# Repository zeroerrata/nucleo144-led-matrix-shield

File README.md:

<p align="center">
  <a href="https://zeroerrata.eu"><picture>
    <source media="(prefers-color-scheme: dark)" srcset="images/zeroerrata-logo-dark.png">
    
  </picture></a>
</p>

<h1 align="center">Nucleo-144 LED matrix shield: 1860 LEDs</h1>

<p align="center"><b>A full-size Nucleo-144 shield with a 31 x 60 matrix of red 0402 LEDs at 45 degrees, driven by constant-current sinks.</b></p>

<p align="center">
  
</p>

<p align="center">

</p>

## About

A display shield for STM32 Nucleo-144 boards (ST morpho connectors CN11 / CN12): 31 columns by 60 rows = 1860 red 0402 LEDs on a 1.75 mm square pitch, every LED turned 45 degrees, filling the whole Nucleo-144 outline. Columns are switched to +5 V by P-MOSFETs selected through four 3-to-8 decoders, rows are sunk by four 16-channel constant-current LED drivers at 5.7 mA per LED, and one column is lit at a time (1/31 duty), refreshed by the Nucleo's MCU.

A dense 4-layer board: rows on the top layer, a solid ground plane, column lanes and the switched column supplies on the inner and bottom layers.

## Features

- 1860 red 0402 LEDs (31 x 60) on a 1.75 mm pitch, rotated 45 degrees for a diamond pattern
- 4 x STP16CP05 constant-current row sinks (5.7 mA per LED, one resistor sets the current)
- 31 x AO3401A P-MOSFET column switches, selected by 4 x 74AHCT138 decoders
- Up to 341 mA in one column from the Nucleo +5 V; driver logic on +3.3 V
- Fits the Nucleo-144 outline and plugs into the ST morpho headers (NUCLEO-F429ZI / F767ZI family)
- One-sided JLCPCB assembly; the morpho sockets are hand-soldered

## Specifications

| | |
|---|---|
| Board | 70.0 x 133.4 mm, 4 copper layers, 1.6 mm |
| Finish | ENIG |
| Parts | 1927 |
| Release | rev 4, 2026-11-27 |
| LED matrix | 31 x 60 = 1860, red, 0402, 1.75 mm pitch |
| Host | STM32 Nucleo-144 (ST morpho CN11 / CN12) |
| Supply | +5 V and +3.3 V from the Nucleo |
| Stackup | 4 layers, 1.6 mm |

## Design values

- 5.7 mA per LED set by the drivers' current resistors; one column of up to 60 LEDs lit at a time: up to 341 mA from the Nucleo +5 V.
- 1/31 duty multiplex, refreshed by the Nucleo MCU.

## Renders

Full resolution: [isometric view](images/renders/hero_iso.png), [top side](images/renders/top.png), [bottom side](images/renders/bottom.png), [low-angle view](images/renders/low.png).

## Files

| Folder | Contents |
|---|---|
| [`kicad/`](kicad) | KiCad 10 project: schematic, board, design rules, project libraries |
| [`docs/`](docs) | [schematic.pdf](docs/schematic.pdf), [board_layers.pdf](docs/board_layers.pdf) |
| [`fabrication/`](fabrication) | Gerber and drill files (zip), bill of materials, pick-and-place |
| [`images/`](images) | renders and copper layer pictures |
| [`analysis/`](analysis) | simulation and analysis results: bringup, dfm, retpath |

## Verification

- MCU pin map checked against the NUCLEO-F429ZI connector tables
- Every result is a prediction from design data; the board has not been measured unless stated.

## How to order

1. Upload `fabrication/gerbers_drill.zip` to your PCB fab; the stackup and finish are in the specifications above.
2. For assembly, use `fabrication/bom_jlcpcb.csv` and `fabrication/cpl_jlcpcb.csv` (JLCPCB format) or the KiCad-format `bom.csv` / `pos.csv`.
3. Check part stock and the footprints against the current data sheets before you order.

## Known issues

Found by the design review of this release; boards built from these files carry them:

- Crosstalk: the bottom drivers' clock couples a 0.73 V spike into their output-enable line (simulated). It stays below the logic threshold, so at worst a nanosecond dimming glitch; firmware avoids it by shifting column data while the outputs are off. Rev 4 re-routes these lines; the crosstalk check passes.
- Reflow balance: from rev 4 the small ground pads connect through thermal reliefs; use a profile with a 60-90 s soak at 150-180 C and inspect the 0402 resistors.
- Parts: rev 4 orders Samtec SSQ-135-01-T-D morpho sockets (second source Sullins PPPC352LFBN-RC) and current 22 uF capacitors; the STP16CP05TTR row drivers had little stock in 2026: buy the drivers before ordering boards.

## Notes

- The renders show the ZeroErrata house look; from rev 4 the fabrication package specifies it too: matte black solder mask, white silkscreen, ENIG.
- The firmware (column scan) is not part of this repository.

## Licence

Released under the [CERN Open Hardware Licence Version 2 - Permissive](LICENSE) (CERN-OHL-P-2.0): use, modify, make and sell it, also commercially. Provided as is, without warranty.

---

<p align="center">
  Designed by <a href="https://zeroerrata.eu"><b>ZeroErrata</b></a>: PCB design, verified before it is ordered.<br>
  <a href="https://zeroerrata.eu">zeroerrata.eu</a> · <a href="mailto:hello@zeroerrata.eu">hello@zeroerrata.eu</a>
</p>

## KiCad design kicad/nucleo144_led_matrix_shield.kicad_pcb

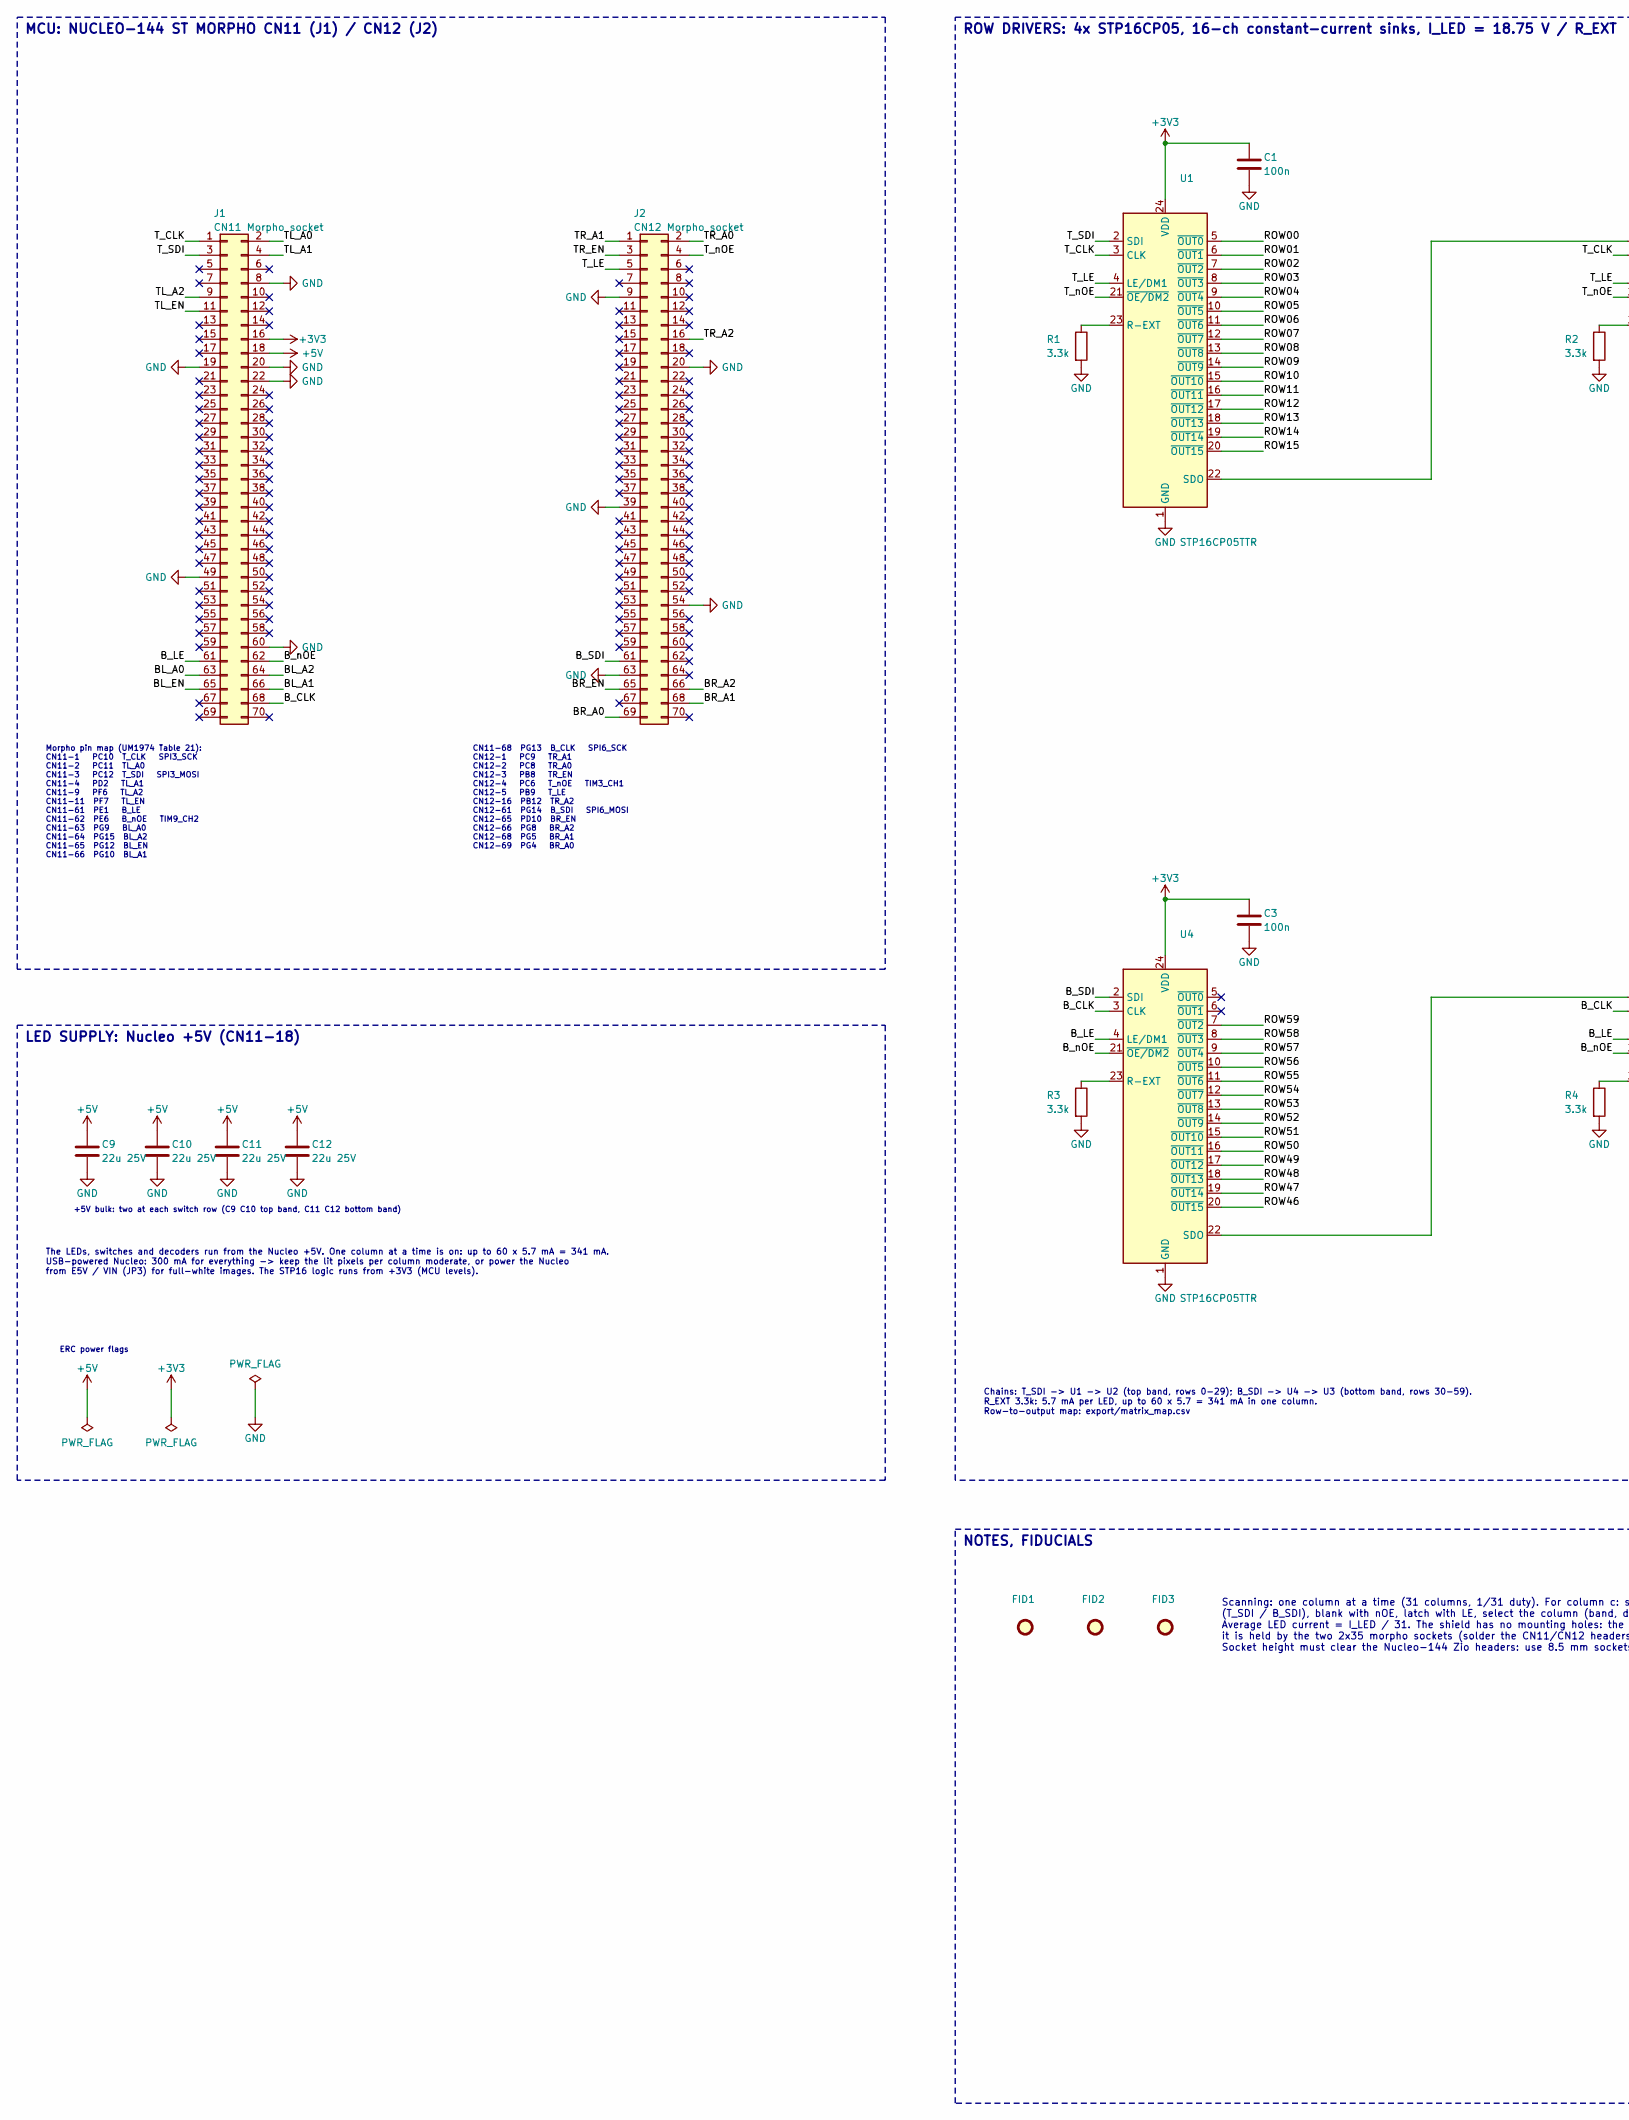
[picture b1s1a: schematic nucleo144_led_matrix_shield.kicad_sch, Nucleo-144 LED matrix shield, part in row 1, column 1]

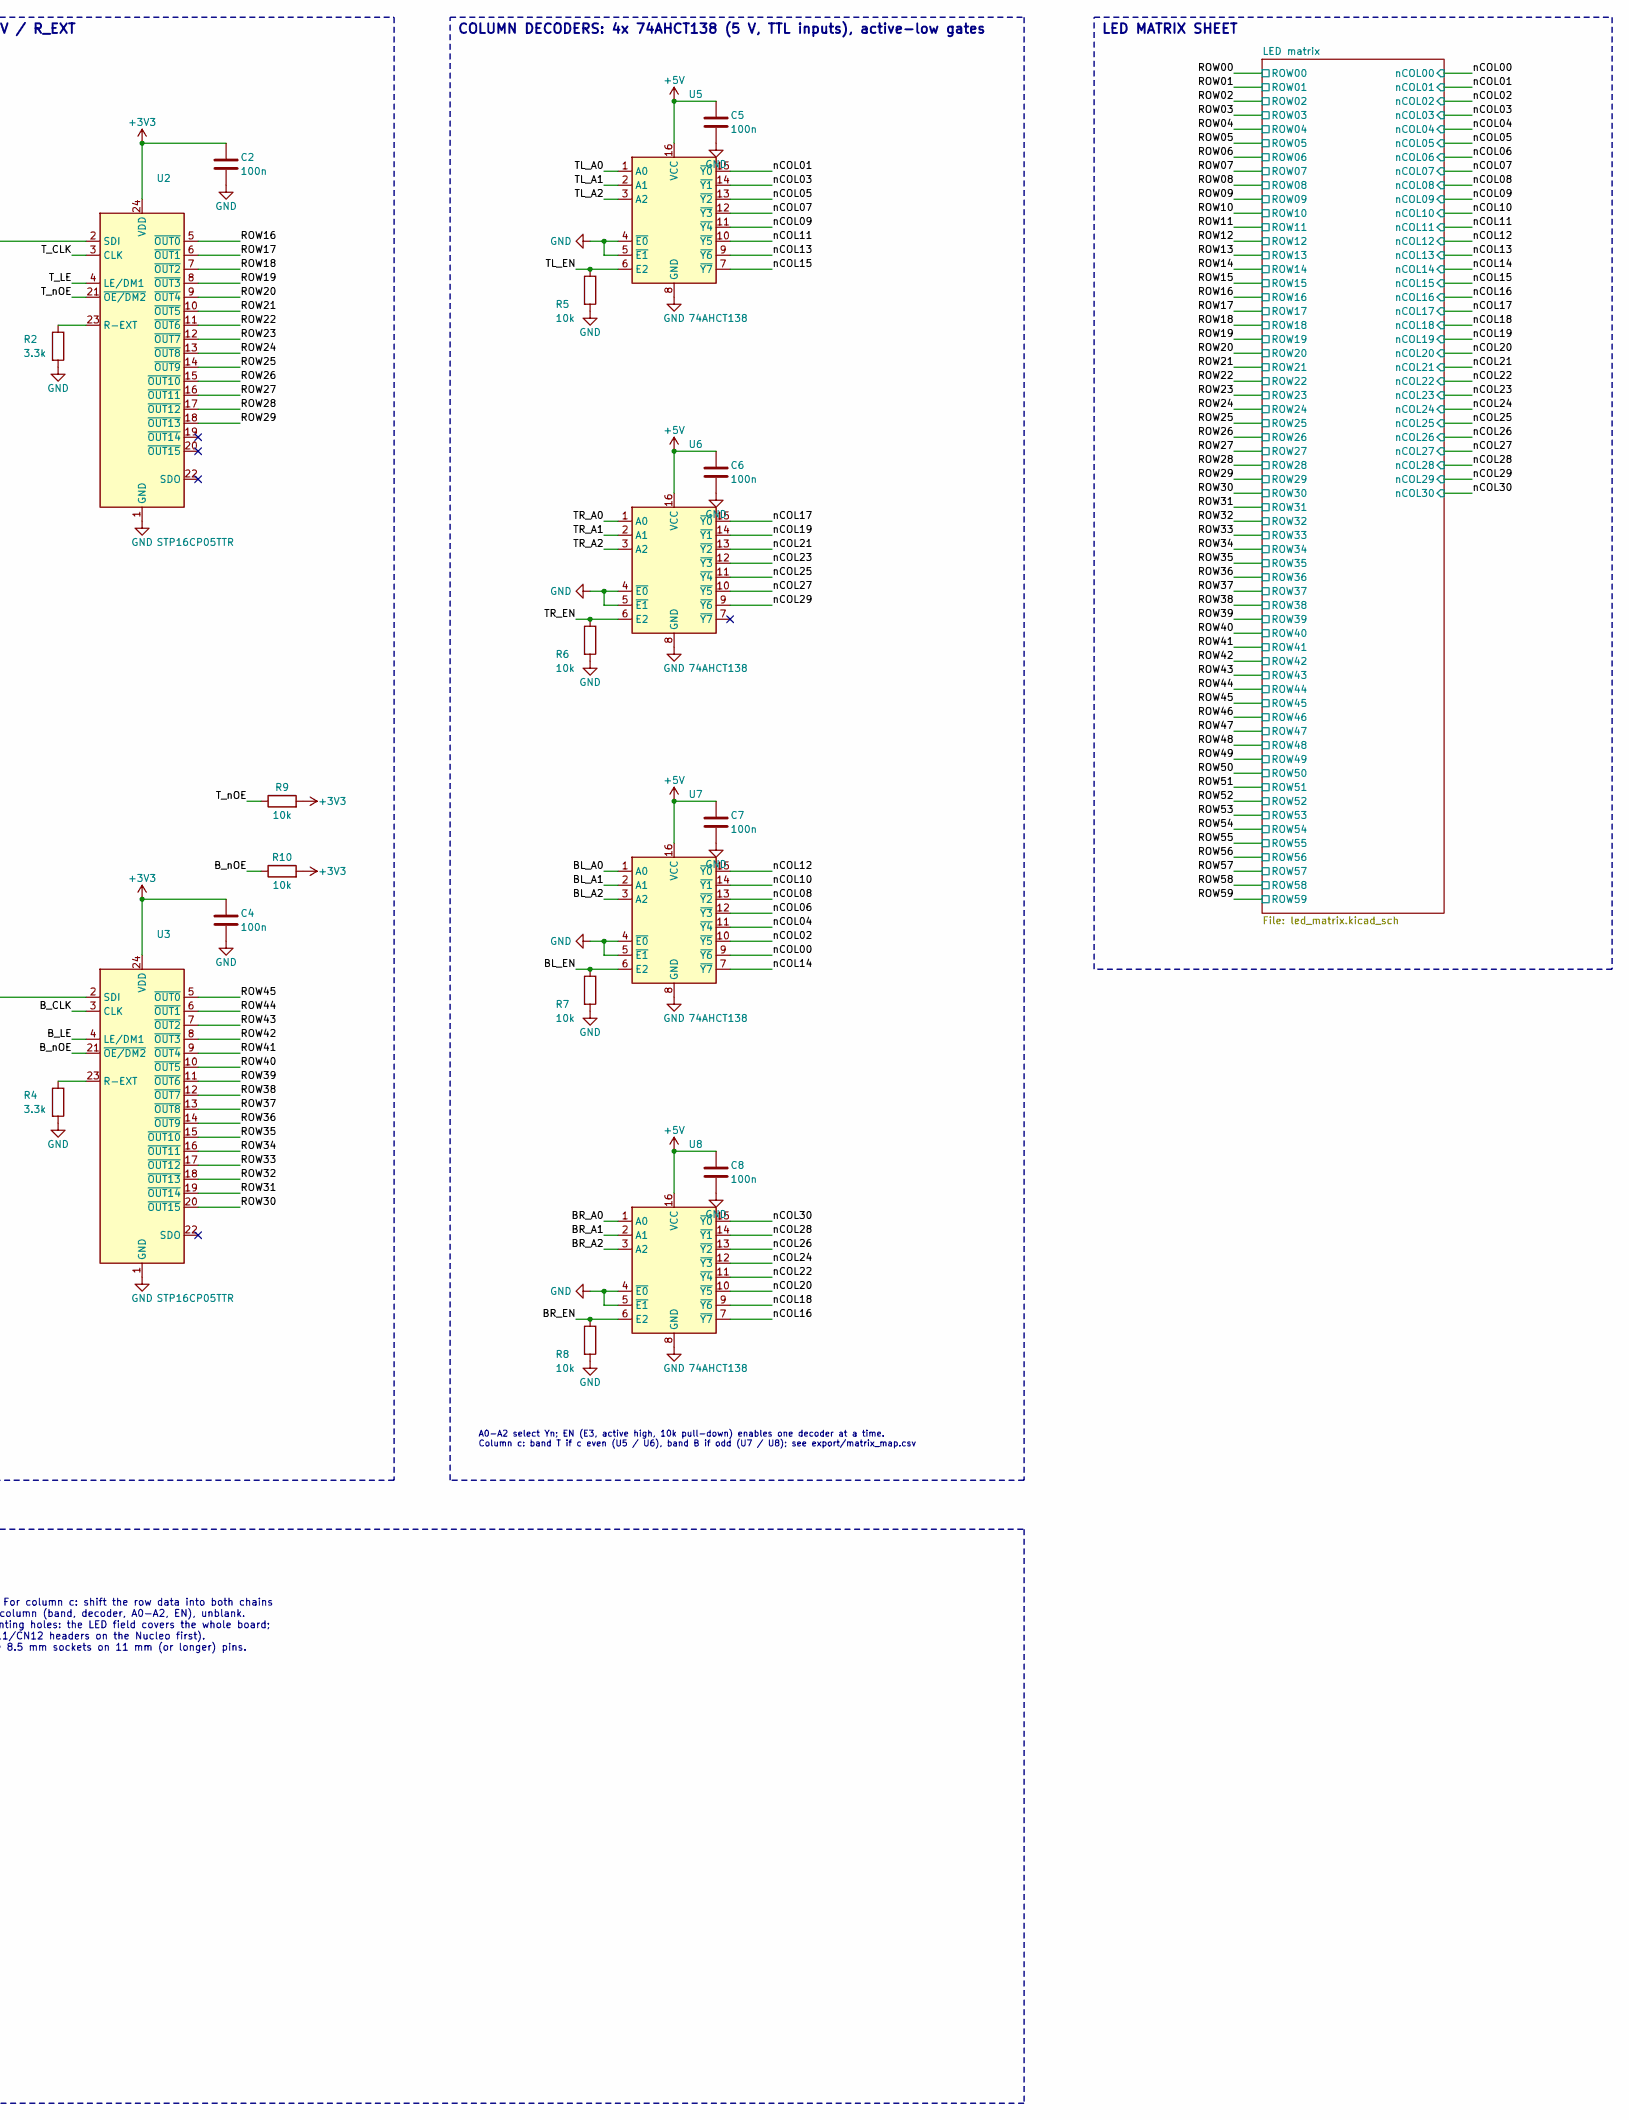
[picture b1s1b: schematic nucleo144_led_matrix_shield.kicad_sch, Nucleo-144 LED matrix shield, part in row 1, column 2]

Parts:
C1, C2, C3, C4, C5, C6, C7, C8: 100n; C_0402_1005Metric; MPN CL05B104KO5NNNC; LCSC C1525
C9, C10, C11, C12: 22u 25V; C_0805_2012Metric; MPN CL21A226MAYNNNE; LCSC C602037
FID1, FID2, FID3: Fiducial; Fiducial_1mm_Mask2mm
J1: CN11 Morpho socket; Morpho_2x35_P2.54mm_Socket_NoInnerAnnulus; MPN SSQ-135-01-T-D; LCSC C7088697
J2: CN12 Morpho socket; Morpho_2x35_P2.54mm_Socket_NoInnerAnnulus; MPN SSQ-135-01-T-D; LCSC C7088697
R1, R2, R3, R4: 3.3k; R_0402_1005Metric; MPN 0402WGF3301TCE; LCSC C25890
R5, R6, R7, R8, R9, R10: 10k; R_0402_1005Metric; MPN 0402WGF1002TCE; LCSC C25744
U1, U2, U3, U4: STP16CP05TTR; TSSOP-24_4.4x7.8mm_P0.65mm; MPN STP16CP05TTR; LCSC C127267
U5, U6, U7, U8: 74AHCT138; TSSOP-16_4.4x5mm_P0.65mm; MPN SN74AHCT138PWR; LCSC C8205

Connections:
+3V3: C1.1, C2.1, C3.1, C4.1, J1.16, R9.2, R10.2, U1.24 (VDD), U2.24 (VDD), U3.24 (VDD), U4.24 (VDD)
+5V: C5.1, C6.1, C7.1, C8.1, C9.1, C10.1, C11.1, C12.1, J1.18, U5.16 (VCC), U6.16 (VCC), U7.16 (VCC), U8.16 (VCC); also elsewhere on the board
/BL_A0: J1.63, U7.1 (A0)
/BL_A1: J1.66, U7.2 (A1)
/BL_A2: J1.64, U7.3 (A2)
/BL_EN: J1.65, R7.1, U7.6 (E2)
/BR_A0: J2.69, U8.1 (A0)
/BR_A1: J2.68, U8.2 (A1)
/BR_A2: J2.66, U8.3 (A2)
/BR_EN: J2.65, R8.1, U8.6 (E2)
/B_CLK: J1.68, U3.3 (CLK), U4.3 (CLK)
/B_LE: J1.61, U3.4 (LE/DM1), U4.4 (LE/DM1)
/B_SDI: J2.61, U4.2 (SDI)
/B_nOE: J1.62, R10.1, U3.21 (~OE/DM2), U4.21 (~OE/DM2)
/ROW00: U1.5 (~OUT0); also elsewhere on the board
/ROW01: U1.6 (~OUT1); also elsewhere on the board
/ROW02: U1.7 (~OUT2); also elsewhere on the board
/ROW03: U1.8 (~OUT3); also elsewhere on the board
/ROW04: U1.9 (~OUT4); also elsewhere on the board
/ROW05: U1.10 (~OUT5); also elsewhere on the board
/ROW06: U1.11 (~OUT6); also elsewhere on the board
/ROW07: U1.12 (~OUT7); also elsewhere on the board
/ROW08: U1.13 (~OUT8); also elsewhere on the board
/ROW09: U1.14 (~OUT9); also elsewhere on the board
/ROW10: U1.15 (~OUT10); also elsewhere on the board
/ROW11: U1.16 (~OUT11); also elsewhere on the board
/ROW12: U1.17 (~OUT12); also elsewhere on the board
/ROW13: U1.18 (~OUT13); also elsewhere on the board
/ROW14: U1.19 (~OUT14); also elsewhere on the board
/ROW15: U1.20 (~OUT15); also elsewhere on the board
/ROW16: U2.5 (~OUT0); also elsewhere on the board
/ROW17: U2.6 (~OUT1); also elsewhere on the board
/ROW18: U2.7 (~OUT2); also elsewhere on the board
/ROW19: U2.8 (~OUT3); also elsewhere on the board
/ROW20: U2.9 (~OUT4); also elsewhere on the board
/ROW21: U2.10 (~OUT5); also elsewhere on the board
/ROW22: U2.11 (~OUT6); also elsewhere on the board
/ROW23: U2.12 (~OUT7); also elsewhere on the board
/ROW24: U2.13 (~OUT8); also elsewhere on the board
/ROW25: U2.14 (~OUT9); also elsewhere on the board
/ROW26: U2.15 (~OUT10); also elsewhere on the board
/ROW27: U2.16 (~OUT11); also elsewhere on the board
/ROW28: U2.17 (~OUT12); also elsewhere on the board
/ROW29: U2.18 (~OUT13); also elsewhere on the board
/ROW30: U3.20 (~OUT15); also elsewhere on the board
/ROW31: U3.19 (~OUT14); also elsewhere on the board
/ROW32: U3.18 (~OUT13); also elsewhere on the board
/ROW33: U3.17 (~OUT12); also elsewhere on the board
/ROW34: U3.16 (~OUT11); also elsewhere on the board
/ROW35: U3.15 (~OUT10); also elsewhere on the board
/ROW36: U3.14 (~OUT9); also elsewhere on the board
/ROW37: U3.13 (~OUT8); also elsewhere on the board
/ROW38: U3.12 (~OUT7); also elsewhere on the board
/ROW39: U3.11 (~OUT6); also elsewhere on the board
/ROW40: U3.10 (~OUT5); also elsewhere on the board
/ROW41: U3.9 (~OUT4); also elsewhere on the board
/ROW42: U3.8 (~OUT3); also elsewhere on the board
/ROW43: U3.7 (~OUT2); also elsewhere on the board
/ROW44: U3.6 (~OUT1); also elsewhere on the board
/ROW45: U3.5 (~OUT0); also elsewhere on the board
/ROW46: U4.20 (~OUT15); also elsewhere on the board
/ROW47: U4.19 (~OUT14); also elsewhere on the board
/ROW48: U4.18 (~OUT13); also elsewhere on the board
/ROW49: U4.17 (~OUT12); also elsewhere on the board
/ROW50: U4.16 (~OUT11); also elsewhere on the board
/ROW51: U4.15 (~OUT10); also elsewhere on the board
/ROW52: U4.14 (~OUT9); also elsewhere on the board
/ROW53: U4.13 (~OUT8); also elsewhere on the board
/ROW54: U4.12 (~OUT7); also elsewhere on the board
/ROW55: U4.11 (~OUT6); also elsewhere on the board
/ROW56: U4.10 (~OUT5); also elsewhere on the board
/ROW57: U4.9 (~OUT4); also elsewhere on the board
/ROW58: U4.8 (~OUT3); also elsewhere on the board
/ROW59: U4.7 (~OUT2); also elsewhere on the board
/TL_A0: J1.2, U5.1 (A0)
/TL_A1: J1.4, U5.2 (A1)
/TL_A2: J1.9, U5.3 (A2)
/TL_EN: J1.11, R5.1, U5.6 (E2)
/TR_A0: J2.2, U6.1 (A0)
/TR_A1: J2.1, U6.2 (A1)
/TR_A2: J2.16, U6.3 (A2)
/TR_EN: J2.3, R6.1, U6.6 (E2)
/T_CLK: J1.1, U1.3 (CLK), U2.3 (CLK)
/T_LE: J2.5, U1.4 (LE/DM1), U2.4 (LE/DM1)
/T_SDI: J1.3, U1.2 (SDI)
/T_nOE: J2.4, R9.1, U1.21 (~OE/DM2), U2.21 (~OE/DM2)
/nCOL00: U7.9 (~Y6); also elsewhere on the board
/nCOL01: U5.15 (~Y0); also elsewhere on the board
/nCOL02: U7.10 (~Y5); also elsewhere on the board
/nCOL03: U5.14 (~Y1); also elsewhere on the board
/nCOL04: U7.11 (~Y4); also elsewhere on the board
/nCOL05: U5.13 (~Y2); also elsewhere on the board
/nCOL06: U7.12 (~Y3); also elsewhere on the board
/nCOL07: U5.12 (~Y3); also elsewhere on the board
/nCOL08: U7.13 (~Y2); also elsewhere on the board
/nCOL09: U5.11 (~Y4); also elsewhere on the board
/nCOL10: U7.14 (~Y1); also elsewhere on the board
/nCOL11: U5.10 (~Y5); also elsewhere on the board
/nCOL12: U7.15 (~Y0); also elsewhere on the board
/nCOL13: U5.9 (~Y6); also elsewhere on the board
/nCOL14: U7.7 (~Y7); also elsewhere on the board
/nCOL15: U5.7 (~Y7); also elsewhere on the board
/nCOL16: U8.7 (~Y7); also elsewhere on the board
/nCOL17: U6.15 (~Y0); also elsewhere on the board
/nCOL18: U8.9 (~Y6); also elsewhere on the board
/nCOL19: U6.14 (~Y1); also elsewhere on the board
/nCOL20: U8.10 (~Y5); also elsewhere on the board
/nCOL21: U6.13 (~Y2); also elsewhere on the board
/nCOL22: U8.11 (~Y4); also elsewhere on the board
/nCOL23: U6.12 (~Y3); also elsewhere on the board
/nCOL24: U8.12 (~Y3); also elsewhere on the board
/nCOL25: U6.11 (~Y4); also elsewhere on the board
/nCOL26: U8.13 (~Y2); also elsewhere on the board
/nCOL27: U6.10 (~Y5); also elsewhere on the board
/nCOL28: U8.14 (~Y1); also elsewhere on the board
/nCOL29: U6.9 (~Y6); also elsewhere on the board
/nCOL30: U8.15 (~Y0); also elsewhere on the board
GND: C1.2, C2.2, C3.2, C4.2, C5.2, C6.2, C7.2, C8.2, C9.2, C10.2, C11.2, C12.2, J1.8, J1.19, J1.20, J1.22, J1.49, J1.60, J2.9, J2.20, J2.39, J2.54, J2.63, R1.2, R2.2, R3.2, R4.2, R5.2, R6.2, R7.2, R8.2, U1.1 (GND), U2.1 (GND), U3.1 (GND), U4.1 (GND), U5.4 (~E0), U5.5 (~E1), U5.8 (GND), U6.4 (~E0), U6.5 (~E1), U6.8 (GND), U7.4 (~E0), U7.5 (~E1), U7.8 (GND), U8.4 (~E0), U8.5 (~E1), U8.8 (GND)
unnamed: R1.1, U1.23 (R-EXT)
unnamed: U1.22 (SDO), U2.2 (SDI)
unnamed: R2.1, U2.23 (R-EXT)
unnamed: R4.1, U3.23 (R-EXT)
unnamed: U3.2 (SDI), U4.22 (SDO)
unnamed: R3.1, U4.23 (R-EXT)

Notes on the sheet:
MCU: NUCLEO-144 ST MORPHO CN11 (J1) / CN12 (J2)
Morpho pin map (UM1974 Table 21): CN11-1 PC10 T_CLK SPI3_SCK CN11-2 PC11 TL_A0 CN11-3 PC12 T_SDI SPI3_MOSI CN11-4 PD2 TL_A1 CN11-9 PF6 TL_A2 CN11-11 PF7 TL_EN CN11-61 PE1 B_LE CN11-62 PE6 B_nOE TIM9_CH2 CN11-63 PG9 BL_A0 CN11-64 PG15 BL_A2 CN11-65 PG12 BL_EN CN11-66 PG10 BL_A1
CN11-68 PG13 B_CLK SPI6_SCK CN12-1 PC9 TR_A1 CN12-2 PC8 TR_A0 CN12-3 PB8 TR_EN CN12-4 PC6 T_nOE TIM3_CH1 CN12-5 PB9 T_LE CN12-16 PB12 TR_A2 CN12-61 PG14 B_SDI SPI6_MOSI CN12-65 PD10 BR_EN CN12-66 PG8 BR_A2 CN12-68 PG5 BR_A1 CN12-69 PG4 BR_A0
ROW DRIVERS: 4x STP16CP05, 16-ch constant-current sinks, I_LED = 18.75 V / R_EXT
Chains: T_SDI -> U1 -> U2 (top band, rows 0-29); B_SDI -> U4 -> U3 (bottom band, rows 30-59). R_EXT 3.3k: 5.7 mA per LED, up to 60 x 5.7 = 341 mA in one column. Row-to-output map: export/matrix_map.csv
COLUMN DECODERS: 4x 74AHCT138 (5 V, TTL inputs), active-low gates
A0-A2 select Yn; EN (E3, active high, 10k pull-down) enables one decoder at a time. Column c: band T if c even (U5 / U6), band B if odd (U7 / U8); see export/matrix_map.csv
LED MATRIX SHEET
LED SUPPLY: Nucleo +5V (CN11-18)
+5V bulk: two at each switch row (C9 C10 top band, C11 C12 bottom band)
The LEDs, switches and decoders run from the Nucleo +5V. One column at a time is on: up to 60 x 5.7 mA = 341 mA. USB-powered Nucleo: 300 mA for everything -> keep the lit pixels per column moderate, or power the Nucleo from E5V / VIN (JP3) for full-white images. The STP16 logic runs from +3V3 (MCU 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
ERC power flags
NOTES, FIDUCIALS
Scanning: one column at a time (31 columns, 1/31 duty). For column c: shift the row data into both chains (T_SDI / B_SDI), blank with nOE, latch with LE, select the column (band, decoder, A0-A2, EN), unblank. Average LED current = I_LED / 31. The shield has no mounting holes: the LED field covers t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

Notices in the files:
parts and their libraries:
LICENSE: CERN-OHL-S-2.0
